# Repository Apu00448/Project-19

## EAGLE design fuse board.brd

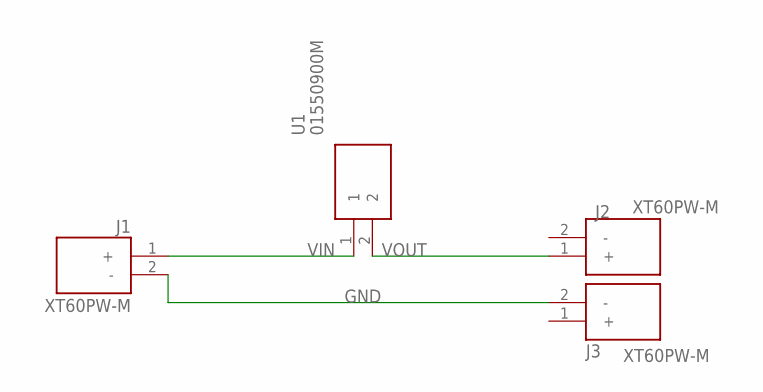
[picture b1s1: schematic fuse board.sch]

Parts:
J1, J2, J3: XT60PW-M; AMASS_XT60PW-M
U1: 01550900M; 0154.250DR

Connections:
GND: J1.2 (-), J3.2 (-)
VIN: J1.1 (+), U1.1
VOUT: J2.1 (+), U1.2

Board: 2 copper layers, 4 parts (0 on the bottom side), 3 nets, no tracks yet.

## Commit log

2024-01-03 Fuse Board- Eagle
